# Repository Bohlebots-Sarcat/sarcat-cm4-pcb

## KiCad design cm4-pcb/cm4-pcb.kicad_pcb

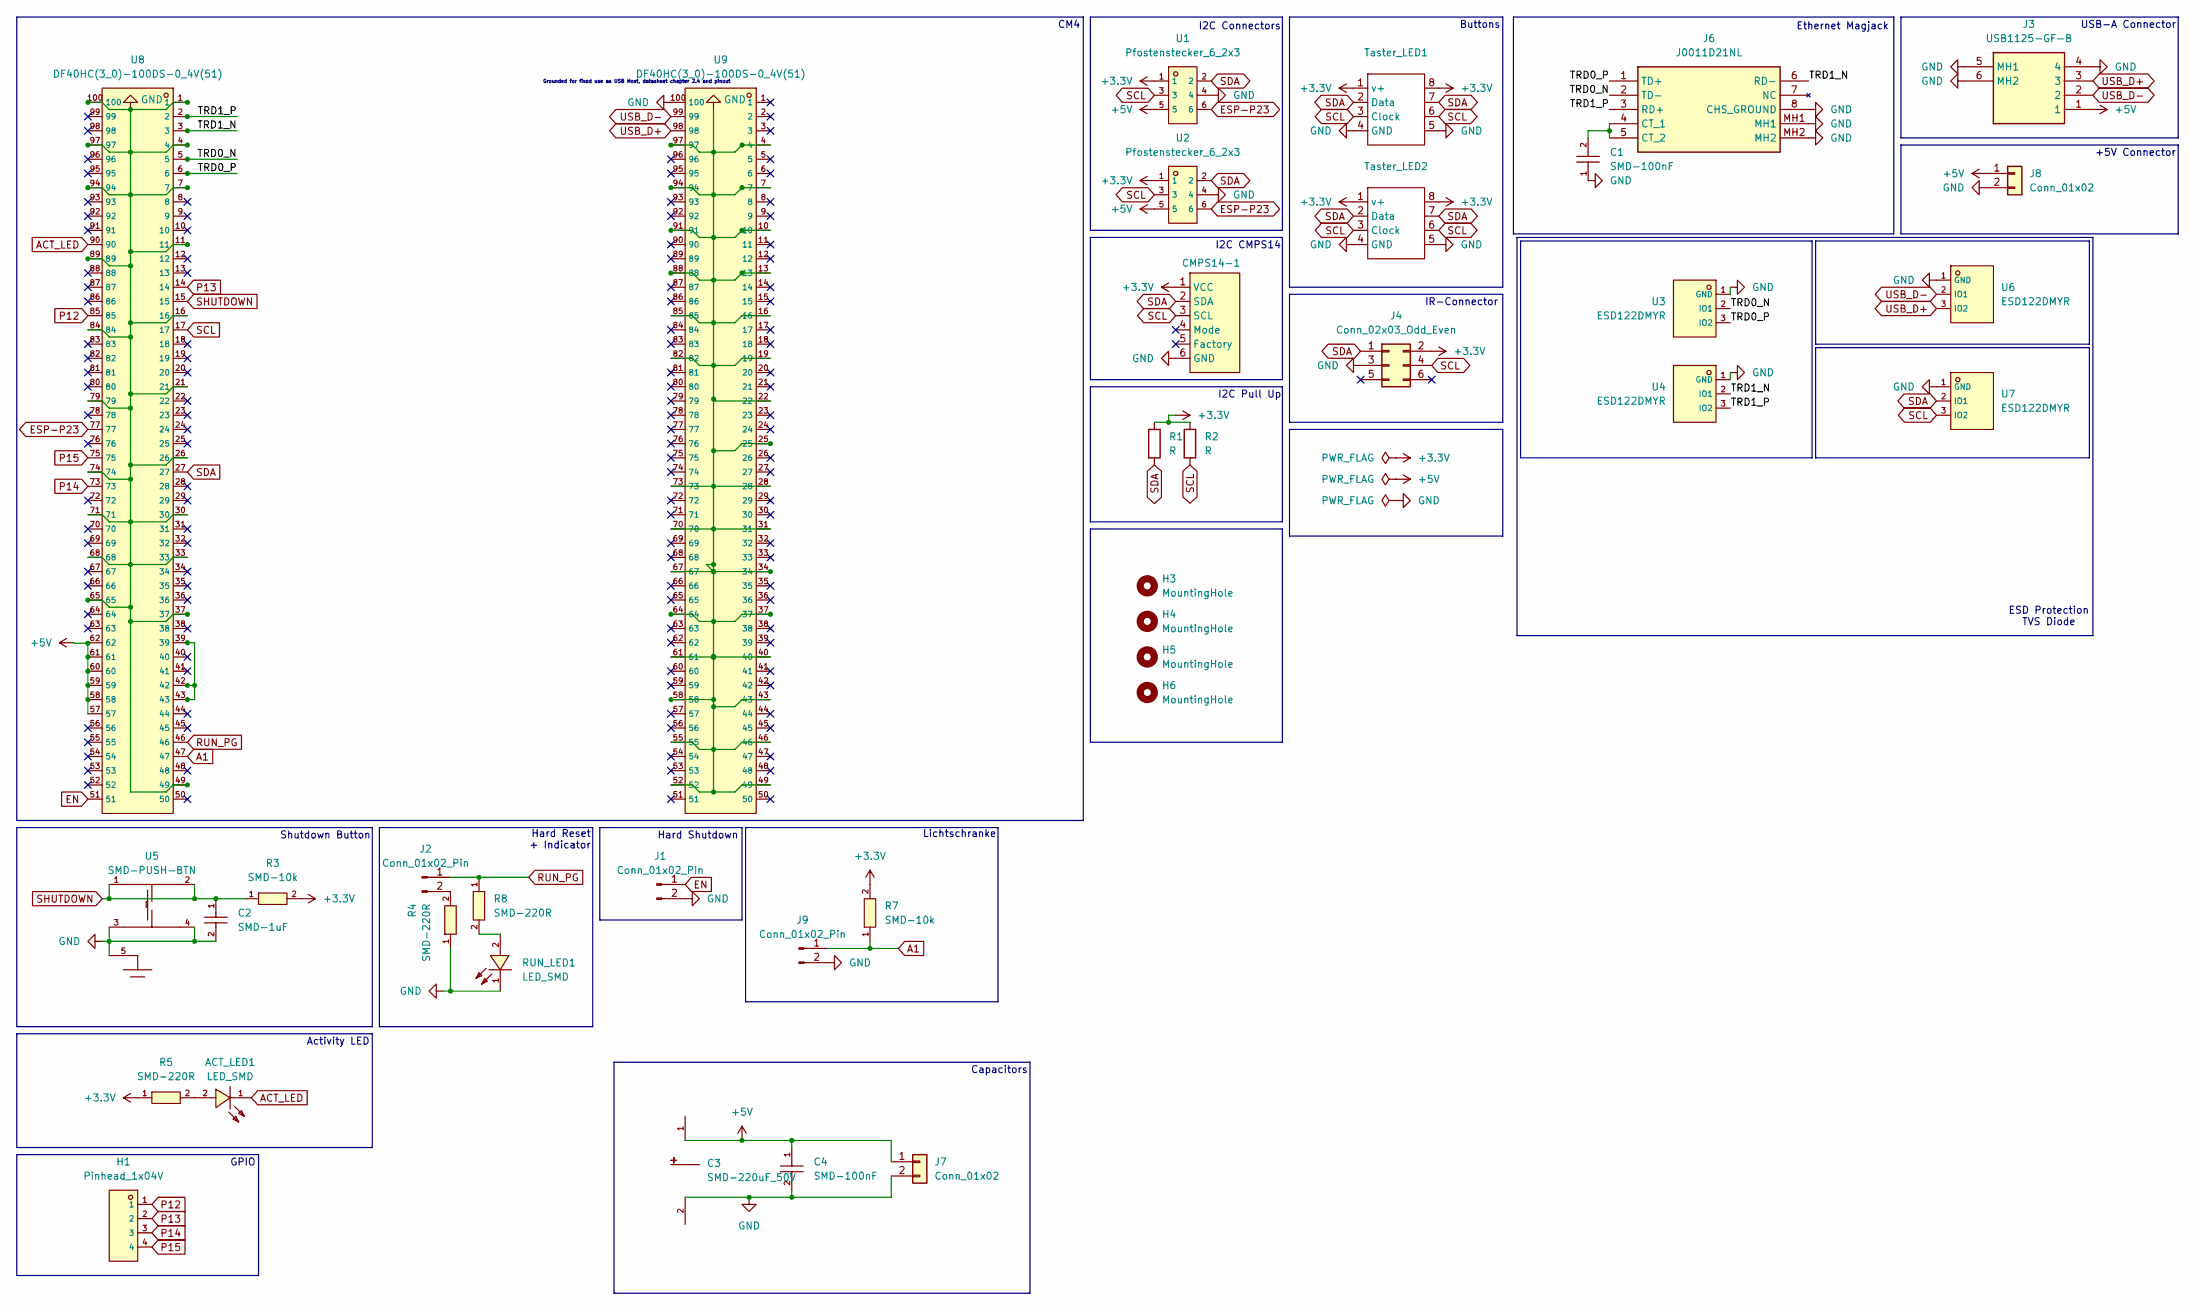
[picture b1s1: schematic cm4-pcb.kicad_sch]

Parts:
ACT_LED1: LED_SMD; LED-SMD_L1.7-W0.6-RD; LCSC C125113
C1, C4: SMD-100nF; C0603; LCSC C30926
C2: SMD-1uF; C0603; LCSC C1592
C3: SMD-220uF_50V; CAP-SMD_BD10.0-L10.3-W10.3-LS11.3-FD; LCSC C125977
CMPS14-1: CMPS14
H1: Pinhead_1x04V; HDR-TH_4P-P2.54-V-M-1; LCSC C920779
H3, H4, H5, H6: MountingHole; MountingHole_4.3mm_M4
J1, J2, J9: Conn_01x02_Pin; PinHeader_1x02_P2.54mm_Vertical
J3: USB1125-GF-B; USB1125GFB; Mouser Part Number 640-USB1125-GF-B
J4: Conn_02x03_Odd_Even; PinHeader_2x03_P2.54mm_Vertical
J6: J0011D21NL; Mouser Part Number 673-J0011D21NL
J7, J8: Conn_01x02; PinHeader_1x02_P2.54mm_Vertical
R1, R2: R; R_THT
R3, R7: SMD-10k; R0603; LCSC C25804
R4, R5, R8: SMD-220R; R0603; LCSC C217883
RUN_LED1: LED_SMD; LED-SMD_L1.7-W0.6-RD; LCSC C125113
Taster_LED1, Taster_LED2: TASTER_LED
U1, U2: Pfostenstecker_6_2x3; HDR-TH_6P-P2.54-V-F-R2-C3-S2.54-4; LCSC C5372863
U3, U4, U6, U7: ESD122DMYR; X2SON-3_L1.3-W0.6-L; LCSC C1975871
U5: SMD-PUSH-BTN; SW-TH_5P-L6.0-W6.0-P4.50-LS6.5; LCSC C470256
U8, U9: DF40HC(3_0)-100DS-0_4V(51); CONN-SMD_DF40HC-3.0-100DS-0.4V-51; LCSC C424649

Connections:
+3.3V: CMPS14-1.1 (VCC), J4.2, R1.1, R2.1, R3.2, R5.1, R7.2, Taster_LED1.1 (v+), Taster_LED1.8, Taster_LED2.1 (v+), Taster_LED2.8, U1.1, U2.1
+5V: C3.1, C4.1, J3.1, J7.1, J8.1, U1.5, U2.5, U8.57, U8.58, U8.59, U8.60, U8.61, U8.62
/TRD0_N: J6.2 (TD-), U3.2 (IO1), U8.5
/TRD0_P: J6.1 (TD+), U3.3 (IO2), U8.6
/TRD1_N: J6.6 (RD-), U4.2 (IO1), U8.3
/TRD1_P: J6.3 (RD+), U4.3 (IO2), U8.2
A1: J9.1, R7.1, U8.47
ACT_LED: ACT_LED1.1 (K), U8.90
EN: J1.1, U8.51
ESP-P23: U1.6, U2.6, U8.77
GND: C1.1, C2.2, C3.2, C4.2, CMPS14-1.6 (GND), J1.2, J3.4, J3.5 (MH1), J3.6 (MH2), J4.3, J6.8 (CHS_GROUND), J6.MH1, J6.MH2, J7.2, J8.2, J9.2, R4.1, RUN_LED1.1 (K), Taster_LED1.4 (GND), Taster_LED1.5, Taster_LED2.4 (GND), Taster_LED2.5, U1.4, U2.4, U3.1 (GND), U4.1 (GND), U5.3, U5.4, U5.5, U6.1 (GND), U7.1 (GND), U8.1, U8.4, U8.7, U8.11, U8.16, U8.21, U8.26, U8.30, U8.33, U8.37, U8.49, U8.65, U8.68, U8.71, U8.74, U8.79, U8.84, U8.89, U8.94, U8.97, U8.100, U9.4, U9.7, U9.10, U9.13, U9.16, U9.19, U9.22, U9.25, U9.28, U9.31, U9.34, U9.37, U9.40, U9.43, U9.46, U9.49, U9.52, U9.55, U9.58, U9.61, U9.64, U9.67, U9.70, U9.73, U9.82, U9.85, U9.88, U9.91, U9.94, U9.97, U9.100
unnamed: ACT_LED1.2 (A), R5.2
unnamed: J2.2, R4.2
unnamed: C1.2, J6.4 (CT_1), J6.5 (CT_2)
unnamed: R8.2, RUN_LED1.2 (A)
unnamed: U8.39, U8.42, U8.43
P12: H1.1, U8.85
P13: H1.2, U8.14
P14: H1.3, U8.73
P15: H1.4, U8.75
RUN_PG: J2.1, R8.1, U8.46
SCL: CMPS14-1.3 (SCL), J4.4, R2.2, Taster_LED1.3 (Clock), Taster_LED1.6, Taster_LED2.3 (Clock), Taster_LED2.6, U1.3, U2.3, U7.3 (IO2), U8.17
SDA: CMPS14-1.2 (SDA), J4.1, R1.2, Taster_LED1.2 (Data), Taster_LED1.7, Taster_LED2.2 (Data), Taster_LED2.7, U1.2, U2.2, U7.2 (IO1), U8.27
SHUTDOWN: C2.1, R3.1, U5.1, U5.2, U8.15
USB_D+: J3.3, U6.3 (IO2), U9.98
USB_D-: J3.2, U6.2 (IO1), U9.99

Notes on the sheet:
Ethernet Magjack
I2C Pull Up
I2C Connectors
USB-A Connector
Lichtschranke
Grounded for fixed use as USB Host, datasheet chapter 2.4 and pinout
Hard Shutdown
Hard Reset + Indicator
GPIO
I2C CMPS14
Shutdown Button
ESD Protection TVS Diode
+5V Connector
IR-Connector
Buttons
Activity LED
Capacitors
CM4

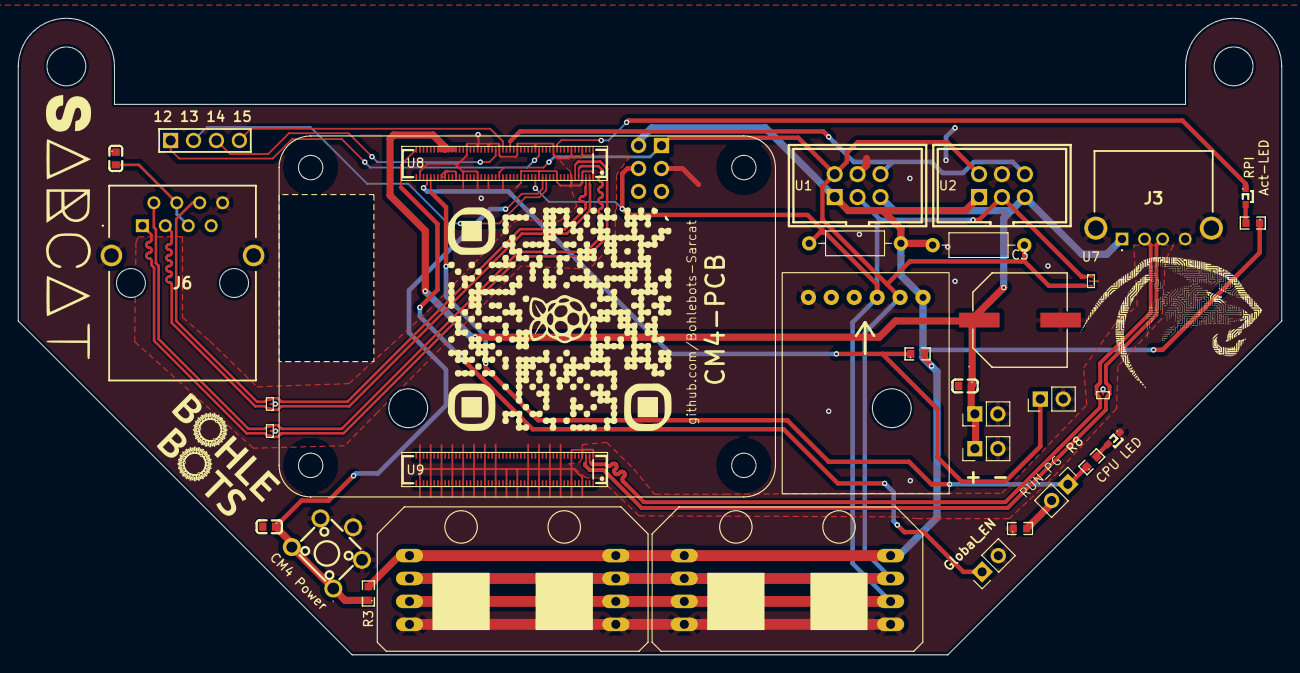
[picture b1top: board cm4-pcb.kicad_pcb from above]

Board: 2 copper layers, 140.0 x 70.5 mm, 38 parts (1 on the bottom side), 26 nets.

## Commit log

2024-07-13 CM4 Library
2024-07-13 Configured Library
2024-07-13 added cmps14
2024-07-16 rerouted gnd and added NC flag
2024-07-17 Added additional I2C Pullup resistor
2024-07-18 Shutdown button
2024-07-18 Activity LED + Reset Pins + GPIO Pins
2024-07-18 Ethernet
2024-07-18 Added USB Connector lub
2024-07-18 Added USB Connector
2024-07-19 Added Power Flags + set ERC Rules
2024-07-21 PCB Placement
2024-07-21 Added TVS Diodes
2024-07-22 V1.0
2024-07-22 V1.1
2024-07-22 Added +5V Capacitors
2024-07-22 Smaller Footprint
2024-07-22 V2.0
2024-07-22 3D Shapes
2024-07-24 Moved Diff. Pair Routes for Crosstalk
2024-07-26 Added Ethernet Library
2024-07-26 Changed Ethernet Magjack + some layout changes
2024-07-26 Adjusted GND Layer for Antenna
2024-07-27 Remove ESD Diodes
2024-07-27 Added ESD122 TVS Diodes
2024-07-27 Added library
2024-07-27 Changed TVS Diodes
2024-07-29 Added extra gnd zones to ensure right impendance for USB+Ethernet
2024-07-29 Modified GND zones
2024-07-29 Cleanup
2024-07-30 Added 5v Connector
2024-07-30 Fixed Traces
2024-08-01 Pins Analog Input
2024-08-04 fixed trace length matching
2024-08-06 Added AN Pullup resistor
2024-08-24 JLCPCB Assemly
2024-09-12 Added visual cm4 footprint to sarcat library
2024-09-12 Fixed connections for cm4 connectors
2024-09-17 Changed cm4 connectors + some solder pads
2024-09-26 Replaced 100R with 220R on LED
2024-10-01 Production
